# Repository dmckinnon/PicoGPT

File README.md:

# PicoGPT
I’ve wanted to learn more about the optimisation techniques that go into running modern LLMs on specialised hardware for a long time, so I recently did a technical deep dive. This involved creating and training a small (few megabytes) GPT-architecture model, which got me thinking: could I optimise such a model to run on something small? What's the smallest thing I could get a reasonable GPT to run on? 

Lo and behold, I give you a Generative Pretrained Transformer running on an ARM Cortex M33, at ~50 tokens per second generation. Let's dive in to how I achieved this.

## Contents
- [Introduction](#introduction)
- [Model structure, size, and training](#model-structure-size-and-training)
- [Porting from tflite to C++](#porting-from-tflite-to-c)
- [Can this run at all](#can-this-run-at-all)
- [Optimisations](#optimisations)
- [Circuit design and fabrication](#circuit-design-and-fabrication)
- [Conclusion](#conclusion)
- [Usage](#usage)

## Introduction
To learn deeply about LLMs I went to none other than [Karpathy](https://karpathy.ai/), his [youtube series](https://www.youtube.com/playlist?list=PLAqhIrjkxbuWI23v9cThsA9GvCAUhRvKZ) on basic LLM architecture, and of course, his [NanoGPT repository](https://github.com/karpathy/nanogpt). This is an excellent way to learn as Karpathy is clear, goes through simple steps, and the repository provides an easy playground to mess with parameters and model structure - one can see which changes affect what, like different numbers of attention heads, layers, context length, etc. The rest of this writeup assumes a considerable familiarity with the topics Karpathy goes over, Language Model architecture, Attention Heads, embedding vectors, tokens, etc. (For those who don't like youtube videos, my own writeups, mostly for my understanding, can be found [elsewhere](https://dmckinnon.github.io/LLMs-overview/) on my [site](https://dmckinnon.github.io/Tokenisation-in-LLMs/))

I'd also recently finished my [Machine Learning Business Card](https://dmckinnon.github.io/ML-Business-card/), and was struck by the thought: _could I make a NanoGPT model that ran on one of these cards?_

There's so many considerations involved in this:
- what does such a model even do? Is it too small to do anything?
- can you get a meaningful model that small? The voice recognition card has 4MB flash and ~200Kb RAM
- The base shakespeare-predictor model that NanoGPT creates, completing phrases from the works of Shakespeare based on character-tokens in a prompt, is ~40~Mb in size, with ~10 million parameters. 
- how fast will this run? My lil chip runs at 125MHz. The NanoGPT example runs on my laptop in functionally-immediate speed, but my laptop has a discrete GPU.

There's two main challenges:
1. Creating a model that can, at minimum, fit into the flash of this chip (4Mb), and probably needs to be smaller, but that also can generate coherent english sentences.
2. Getting such a model to run in real time on this tiny chip 

So, where to start? 

## Model structure, size, and training
First, can we even create a model that's really small and does something useful? I set myself a size budget of 100Kb - as in the model file (all model parameters) could not be larger than this - and twiddled with the base model. This budget comes from being ~half the RAM of the RP2040 - I'm eyeballing and thinking the code won't take much, and then we need some memory for stack, heap, etc, so 100kb seems like a good amount to aim for a priori.\ 
But what should we train it on? 100Kb model, predicting Shakespeare? That's boring, that's not much Shakespeare and also who cares. Some other pithy quotes? Amusing, but no. 

What about ... me? What if we trained the model to regurgitate facts about me? Going back to the business card idea, wouldn't it be great if my business card could just ... speak my resume to people and answer queries about that? 

I loved this idea, so I wrote up my CV, writ small (100Kb model, remember, it's not learning much), to use as the training set. 

### The base model
If we just run the prompts Karpathy has given us, to predict Shakespeare, then we get a model with:
- vocab size 65
- dataset length 1 million
- 6 layers in the model
- 6 attention heads
- 384 embedding dimensions
- ~ 10 million parameters
- ~40Mb in storage as float

### My model
The training data is the following:

```
David studied at UNSW Univeristy of New South Wales from 2012 to 2016\
What did he study?
He studied engineering and mathematics, focusing in robotics and computer vision 
David worked at Microsoft from 2016-2023
What did he work on?
At Microsoft he worked on HoloLens, using feature tracking.
At Microsoft he experimented with constellation tracking and non-inertial tracking
David work at startup Tetra in 2023
At Tetra he worked on ML graph passes, op implementations, and model zoo
David worked at Qualcomm in 2024
At Qualcomm he worked on ML graph passes and op implementations
```

dataset stats:
- length of dataset in characters: 582
- all the unique characters:  ,-.012346?ADHLMNQSTUWabcdefghiklmnoprstuvwxyz
- vocab size: 47 unique tokens, where each token is a single character

Couple notes:
- Why the questions? So that this could be legitimately queried, like a prompt could be those precise questions
- "doesn't this contain a lot of redundancy?". Yes. Yes it does. The tokenizer I'm using tokenises by characters. I want there to be examples where the characters "experimented" follow "he", but also the characters "studied" follow "he", and so on and so forth. 
- This is succinct because the model is 100kb at most, like I really have to squish it down
- Could we have more? Not sure, let's start here. I wasn't sure at the time how good a 100Kb model would be. Worst case is we overfit to this, and if this happens, I'll train on a bigger dataset

I played around with parameters. How many heads? How many embedding dimensions? How many layers? There are so many experiments to run, and I definitely did not exhaustively find the best set of parameters. But that's not my goal - I just want _something that works_. I found that the following worked:

- 1 attention head per layer
- 2 layers
- 32 embedding width
- context length 31, using a sliding window context
- 27,232 parameters
- 107Kb in storage as float

By "worked" here I mean:
- it produced reasonable predictions when prompted ... although to be honest, it's so overfit it's just regurgitating the training data. TODO examples
- it "fits" within the memory budget I have: 100Kb (ok it's 107Kb but this is close enough, I'm going to work with it)

This is a good start! Maybe I want to return to this step for a better model, but this easily fits within the flash we have - 4Mb, the matrices for individual steps fit within the RAM budget, and the results look good. So before I stress too much over getting the perfect model, let's attempt implementation. 

## Porting from tflite to C++
When running the model in NanoGPT's sample.py, there are two parts. One is the actual forward pass of the transformer, which produces a vector of logits, and the other is a loop that runs softmax over these logits, finds the probability of each vocab entry (token), samples from a distribution to get the next token, and then runs the next forward pass over the new token set. 

The first part, the actual forward pass of the transformer, is the model inference and it's here we use the model weights. The rest is just math. So to extract the model - the set of all weights, and structure of tensors and operations - in sample.py I use the following python code, where `model` is the `torch.nn` object whose `forward` function is the transformer pass inside the `mode.py` `generate` function:

```
traced = torch.jit.trace(model, x)
torch.jit.save(traced, "traced_model.pt")
```

This produces a pytorch file. Are we going to manually copy the weights from this? Well, no.\
Pytorch files are not particularly well optimised, having many redundant layers like transposes that are later cancelled by other transposes, or cast ops to int, or whatever:

I'd like to clean this model up, and made it easier to understand, for starters. Qualcomm has this marvellous platform called [Qualcomm AI Hub](https://workbench.aihub.qualcomm.com/) that can [optimise a model for a device](https://workbench.aihub.qualcomm.com/docs/hub/compile_examples.html).\
(Disclosure: no, I'm not sponsored by Qualcomm. I used to work on this product, however, and just genuinely think it's really useful)\
While the device I'm optimising for isn't available - they only have a selection of Qualcomm chips, funnily enough - this doesn't matter. All I'm really hoping to do is to strip the unnecessary layers from the model. We run it through their platform 

and now we have a tflite file! This is considerably cleaner, so the Qualcomm optimisation pass was worth it, even just for readability. From this we can identify the different parts of the transformer in each layer and consider the code for each part. 

### Layernorm
- the [layernorm](https://docs.pytorch.org/docs/2.15/generated/torch.nn.LayerNorm.html) op. Straightforward elementwise mathematical operation. (TFLite does not natively have a Layernorm op, and so breaks this out into constituent operations). This is\
$y=\frac{x-\bold{E}[x]}{\sqrt(Var[x]+\epsilon)}\times\gamma +\beta$\
The point of this operation is to normalise the data after each other operation, so there's a few of these.

```
for (size_t seq = 0; seq < seq_len; seq++) {
    const float* input_row = input + seq * embed_dim;
    float* output_row = output + seq * embed_dim;
    
    // Compute mean
    float mean = 0.0f;
    for (size_t i = 0; i < embed_dim; i++) {
        mean += input_row[i];
    }
    mean /= embed_dim;
    
    // Compute variance
    float variance = 0.0f;
    for (size_t i = 0; i < embed_dim; i++) {
        float diff = input_row[i] - mean;
        variance += diff * diff;
    }
    variance /= embed_dim;
    
    // Normalise
    float inv_std = 1.0f / sqrtf(variance + epsilon);
    for (size_t i = 0; i < embed_dim; i++) {
        output_row[i] = gamma[i] * (input_row[i] - mean) * inv_std + beta[i];
    }
}
```

### Q/K/V
- Q/K/V matrix multiplications with the embedding vectors. Matrix $\times$ vector, simple. By keeping the vectors consecutive in memory, we create a matrix, and can just use our matrix multiplication function to do this:

```
static inline void matmul(
    const float* A, size_t rows_a, size_t cols_a,
    const float* B, size_t cols_b,
    float* C
) {
    for (size_t i = 0; i < rows_a; i++) {
        for (size_t j = 0; j < cols_b; j++) {
            float sum = 0.0f;
            for (size_t k = 0; k < cols_a; k++) {
                sum += A[i * cols_a + k] * B[k * cols_b + j];
            }
            C[i * cols_b + j] = sum;
        }
    }
}

// Then to actually do the QKV projection:

const float* q_weights = qkv_weights;                           // [0:embed_dim, :]
const float* k_weights = qkv_weights + embed_dim * embed_dim;   // [embed_dim:2*embed_dim, :]
const float* v_weights = qkv_weights + 2 * embed_dim * embed_dim; // [2*embed_dim:3*embed_dim, :]

// Project to Query
matmul(input, seq_len, embed_dim, q_weights, embed_dim, query);

// Project to Key
matmul(input, seq_len, embed_dim, k_weights, embed_dim, key);

// Project to Value
matmul(input, seq_len, embed_dim, v_weights, embed_dim, value);
```

### Scaled Self-Attention
- Scaled self-attention\
[image]
This is the key attention equation:\
$Attention(Q, K, V) = softmax(\frac{QK^T}{\sqrt{d_k}})V$\
We could break this down further into a matrix multiplication, a scaling, and another matrix multiplication, but I think it's better to keep it all as one function because then we can smoosh a bunch of things together. 

```
static inline void softmax(float* input, float* output, size_t length) {
    // Find maximum value for numerical stability
    float max_val = input[0];
    for (size_t i = 1; i < length; i++) {
        if (input[i] > max_val) {
            max_val = input[i];
        }
    }
    
    // Compute exponentials and sum
    float sum = 0.0f;
    for (size_t i = 0; i < length; i++) {
        output[i] = expf(input[i] - max_val);
        sum += output[i];
    }
    
    // Normalize
    for (size_t i = 0; i < length; i++) {
        output[i] /= sum;
    }
}

// then to perform attention

const float scale = INV_SQRT_HEAD_DIM; // 1/sqrt(embed_dim)
    
// Compute Q * K^T / root(embed_dim)
// query: [seq_len, embed_dim], key^T: [embed_dim, seq_len] -> scores: [seq_len, seq_len]
for (size_t i = 0; i < seq_len; i++) {
    for (size_t j = 0; j < seq_len; j++) {
        float sum = 0.0f;
        for (size_t k = 0; k < embed_dim; k++) {
            sum += query[i * embed_dim + k] * key[j * embed_dim + k];
        }
        attention_scores[i * seq_len + j] = sum * scale;
    }
}

// Apply causal mask and softmax for each query position
for (size_t i = 0; i < seq_len; i++) {
    float* score_row = attention_scores + i * seq_len;
    
    // Apply causal mask (can only attend to previous and current positions)
    for (size_t j = i + 1; j < seq_len; j++) {
        score_row[j] = -INFINITY;
    }
    
    // Apply softmax to this row
    softmax_inplace(score_row, seq_len);
}

// Apply attention weights to values: output = attention_scores * value
// attention_scores: [seq_len, seq_len], value: [seq_len, embed_dim] -> output: [seq_len, embed_dim]
for (size_t i = 0; i < seq_len; i++) {
    for (size_t j = 0; j < embed_dim; j++) {
        float sum = 0.0f;
        for (size_t k = 0; k < seq_len; k++) {
            sum += attention_scores[i * seq_len + k] * value[k * embed_dim + j];
        }
        output[i * embed_dim + j] = sum;
    }
}

```

### Feed-Forward Network
- Feed Forward Network [image]. This is just a matrix multiplication (`Fully Connected`), a [GELU](https://docs.pytorch.org/docs/2.15/generated/torch.nn.GELU.html) elementwise operation, and then another matrix multiplication. A lot of matrix multiplication happening all over the place, so an obvious point to start improvements.

```
matmul(input, seq_len, embed_dim, up_weights, ffn_dim, hidden);
    
// Apply GELU activation in-place
apply_gelu(hidden, seq_len * ffn_dim);

// Second linear layer: output = hidden * down_weights  
// hidden: [seq_len, ffn_dim], down_weights: [ffn_dim, embed_dim] -> output: [seq_len, embed_dim]
matmul(hidden, seq_len, ffn_dim, down_weights, embed_dim, output);
```

### Residual Skip Connection
This is the `Add` operation joining those two branches together. We take the input to the whole layer, before any attention or feed-forward, and add it with the output of the whole layer.

```
static inline void add_tensors(
    const float* A,
    const float* B,
    float* C,
    size_t length
) {
    // Yeah this one's pretty simple
    // The vectors are so short it's practically not worth optimising
    for (size_t i = 0; i < length; i++) {
        C[i] = A[i] + B[i];
    }
}

// This comes in after FFN, for example
float* ffn_output = ffn_op(arena, normalized_input, up_weights, down_weights, 
                              seq_len, embed_dim, ffn_dim);
size_t total_elements = seq_len * embed_dim;
add_tensors(input, ffn_output, output, total_elements);
    
```

### Gather
This is simply indexing into an array. "Here's some indices for vocab elements, get the vocab elements they refer to".

### Putting it all together
Now all we need to do is connect those parts ... 

```
// inside Attention with residual:
qkv_projection(input, qkv_weights, query, key, value, seq_len, embed_dim);
    
// Step 2: Scaled Dot-Product Attention
scaled_dot_product_attention(query, key, value, attention_output, 
                            attention_scores, seq_len, embed_dim);

// Step 3: Output Projection
attention_output_projection(attention_output, output_weights, final_output, 
                               seq_len, embed_dim);

// Step 4: residual
size_t total_elements = seq_len * embed_dim;
add_tensors(input, attention_output, output, total_elements);

// inside FFN with residual:
layer_norm(input, normalized_input, ln_gamma, ln_beta, seq_len, embed_dim, LAYER_NORM_EPS);
float* ffn_output = ffn_op(arena, normalized_input, up_weights, down_weights, 
                              seq_len, embed_dim, ffn_dim);
size_t total_elements = seq_len * embed_dim;
    add_tensors(input, ffn_output, output, total_elements);

// Running one full layer:
// (repeat for n layers, and update parameters accordingly)
float* attn_output = attention_with_residual(
    arena, input, attn_qkv, attn_out, ln_gamma_1, ln_beta_1,
    seq_len, config->embed_dim
);

// FFN with residual connection
float* layer_output = ffn_with_residual(
    arena, attn_output, ffn_up, ffn_down, ln_gamma_2, ln_beta_2,
    seq_len, config->embed_dim, config->ffn_dim
);

```

and thats the whole model! 

## Can this run at all

Is it actually that simple? Well, let's see if this runs at all. For my first ML-on-business-card I used the [RP2040](https://pip-assets.raspberrypi.com/categories/814-rp2040/documents/RP-008371-DS-1-rp2040-datasheet.pdf), but it does software emulation of floating point hardware - that is, floating point math is actually done with 32-bit integers emulating what a dedicated floating point logic gate circuit would do. Software-floating-point will work, but be slow. Coincidentally, the next generation, the [RP2350]() chip had just come out, and this one came with a FPU coprocessor - floating point hardware! So floating point arithmetic could be performed in a single clock cycle. A dev board was acquired, a compiler was run (and run and run and run and eventually the code compiled), a chip was flashed, aaaaaand ...

|Input context length |	Time per next token |	Tokens/second
|----------------|---------------:|-----------:|
|5 tokens |	25.473 ms |	39.26
|7 tokens |	30.128 ms |	33.19
|10 tokens |	37.315 ms |	26.80
|31 tokens |	92.209 ms |	10.85

10 tokens per second!! For a basic implementation, that's a lot more than I was expecting. I'm ignoring the low context lengths, because those are not particularly useful. We want full sentences, and when a single token is a single character ... 5 characters doesn't get you much. 31 characters does. 

So, what do we do from here? Is this it? It runs, produces sentences, yay done move on?\
Absolutely not! Now we need to see just how fast we can get this model running. The main metric I'll use is tokens per second on prompt processing and decode processing, but as decode is a fixed 31-length sliding window, it doesn't make much of a difference. 

There are a number of optimisations I have in mind: multithreading, unrolling, removing intermediates, RAM residency, quantisation. The next section will go through everything I tried, including failures. 

## Optimisations

There are several benchmarks I'm using here. For some things like matrix multiplication, we can easily create a standalone benchmark. I'm also giving the model a small prompt and generating 100 output tokens based on this prompt, and we'll see how that is affected each time. 

All optimisations were also checked for accuracy, both on numerical benchmarks (computing matrices etc) and also checking token-generation output. While the output logits (the values directly from the final layer) changed slightly, the difference was never enough to change the final probabilities for each token, for the next prediction. Only optimisations that maintain this accuracy are considered. 

There are a couple of optimisations some notice are missing here; namely, quantisation and KV caches. I did consider these and ultimately rejected, and I'll address that briefly:
- Quantisation.\
Quantisation involves squashing my nice and accurate floating points into discrete little int8s. The advantages of this are namely storage - I could have four times as many parameters for the same flash size - and processing speed, as I could use the M33's DSP to do SIMD operations on int8 data, computing 4 results within one clock cycle. However, there's an accuracy cost to quantisation, and given the speeds I ended up getting with floating point, I did not consider the accuracy hit worthwhile at this stage. Perhaps for V2, where I want to attempt a bigger model.
- KV Cache\
One common optimisation in the LLM-implementation field is that of a KV cache. When generating tokens after the prompt, since we have already run over the attention of previous tokens to other previous tokens, this does not need to be recomputed, so we, well, cache the result of this and simply compute the K/V results for any new tokens. I decided against this one. Firstly, when generating tokens, I use a sliding window context of 31 tokens - therefore, any results older than 31 tokens become irrelevant, and we need to recompute the 31-token attention anyway, or do complex cache management. Recomputing is easier. Secondly, 31-token context is simply not large enough to warrant the complexity of a KV cache.

### Cache-coherent matmul
Both attention and Feed-Forward Networks rely on matrix multiplication. My thought was that to optimise for cache-coherency, as matrices tend to be stored linearly, we could write out one row of output at a time - keeping the whole row in cache - and therefore keep one row of matrix $A$ in $C = A\times B$ resident in cache as well, whilst iterating through the columns of B. That second iteration would have cache misses, but no more so than a regular iteration keeping one column of B, iterating through rows of A and rows of output. 

A nice idea in theory; it turns out, from the [datasheet](https://support.arm.com/documentation/100230/latest/) that the ARM Cortex M33, that the RP2350 is based on, has no CPU cache, and therefore ... this is irrelevant. Oh well. A nice idea.

### SRAM Residency
The RP2350 fetches weights from flash and places them into SRAM to do the matrix calculations. There is a 16 KiB cache for this, buuuuut ... what if we avoided that fetch? Each fetch from flash has a delay due to the cache (could have a miss) and the QSPI memory interface. It's not large, but we have 500Kb of SRAM and a 107Kb model. We can fit this entirely within RAM once upon startup - incurring a one-time cost - but then reuse weights with abandon, processing as many new tokens as we see fit without any extra fetch overhead. 

To achieve this, we just use a linker setting: `-DPICO_DEFAULT_BINARY_TYPE=copy_to_ram`\
Or in CMake, `pico_set_binary_type(PicoGPT copy_to_ram)`. \
This then copies all application code and constants, like weights, into SRAM upon boot. We could manually write a copy, but I prefer to not reinvent the wheel (or the memcpy).

Here's the timing, with and without:
|Configuration	|Time per token, 31-token context|	Tokens/s|
|----------------|---------------:|-----------:|
| baseline, flash/XIP|	79.852 ms|	12.52|
|SRAM code + weights|	63.907 ms|	15.65|

A considerable improvement! An expected one, but nonetheless rewarding to see. 

### Unrolling
This is essentially pipelining loops. Consider a standard matmul loop:

```
for (B matrix rows)
    for (A matrix cols)
        for (C matrix position)
            C[i,j] += a*b
```

In the inner-most loop, we do one multiplication, one addition, one store, and then check loop conditions, have a potential branch, and set up the loop again. There's almost as much overhead as there is loop calculation!

What if we were to do more per loop? Consider:

```
for (B matrix rows)
    for (4 A matrix cols)
        for (4 C matrix positions)
            C[i_1,j_1] += a_1*b_1
            C[i_2,j_2] += a_2*b_2
            C[i_3,j_3] += a_3*b_3
            C[i_4,j_4] += a_4*b_4
```

We've essentially batched this matmul, doing 4 at a time. Obviously this requires the size to be divisible by 4, but we know the size a priori so we can make this work. Now we do 4 multiplications and 4 additions per loop overhead! The multiplications in the Floating Point coprocessor take a couple of cycles, but there are multiple floating-point registers we can use so these multiplies can be pipelined so we hide the delay on those registers behind the next multiply:

```
Example with unrolling 2 at a time

Before:
cycle 1: R0 = R1*R2
cycle 2: R0 locked behind second cycle  of multiply, nothing happens
cycle 3: R4 += R0
cycle 4: loop stuff

After:
cycle 1: R0 = R1*R2
cycle 2: R0 locked, R5 = R6*R7
cycle 3: R4 += R0, R5 locked
cycle 4: R8 += R5
cycle 5: loop stuff
```

In this 'after', there's no cycle where we are just waiting - we're always doing something. This may seem small, but recall it's the inner loop of three nested loops so this happens a lot. And that's just one matmul, of three matmuls per layer, for two layers, per token. The time saving should add up. 

Does it? Let's take a look at the results:

|Configuration|	Time/token|	Tokens/s|	Speedup vs flash baseline|
|----------------|---------------:|-----------:|-----------:|
|Flash/XIP baseline|	79.852 ms	|12.52	|1.00×|
|SRAM code + weights|	63.907 ms|	15.65|	1.25×|
|Four-way matmul unrolling: FFN and attention projections|	40.826 ms	|24.49	|1.96×|

As expected, we get gainz. That's enormous though! 

What can be unrolled?\
Any loop, really. Matrix multiplications, elementwise operations like tensor addition or GELU, parts of the softmax function. Unroll everything! I realised later that I had forgotten some of the loops to unroll here, and so our speedup is technically even more.

### Fused Multiply-Accumulate
Can we make the inner loop of matmuls even faster? Until now, this inner loop of the matrix multiplication has been using two instructions: floating point multiply, and floating point add. \
But there's an important feature in this floating point coprocessor: [Fused Multiply-Accumulate](https://pip-assets.raspberrypi.com/categories/1214-rp2350/documents/RP-008373-DS-3-rp2350-datasheet.pdf), also known as `FMA` (Section 3.7.2.4).

This does exactly as it sounds, performing a multiply and accumulate (+=) all in one instruction. This should make our inner loop have half the number of instructions! That's twice as fast! It's a relatively simple change, just a compiler flag:

```
# Specifically, the ffp-contract=on is the FMA.
target_compile_options(PicoGPT PRIVATE
    -Wall -Wextra -O2 -fstack-usage -ffp-contract=on
)
```

And this will replace floating point multiplies followed by accumulates with the single instruction. 

Check results, and note that this is on top of unrolled loops:

|Measurement|	FMA off|	FMA on|	Change in elapsed time|
|----------------|---------------:|-----------:|-----------:|
|Scalar attention-projection matmul	|1.836 ms	|1.624 ms	|11.5% less|
|Four-way attention-projection matmul|	0.945 ms|	1.168 ms|	23.6% more|
|Four-way FFN-up matmul	|3.767 ms|	4.659 ms	|23.7% more|
|Generate 100 tokens, inference only	|3.432 s|	3.612 s|	5.2% more|

Oh.\
This is slower, overall.\
Hmm. \
Why is this slower?

I dug a bit but not enough to properly figure it out. It was faster than the single-multiple-accumulate per loop, but not faster than unrolling. My theory is that it uses more registers and slowed down the unrolled version with register swaps? No evidence to support this. I could dig into the assembly, but we got such a massive win from unrolling and there's more to try that if all else fails I'll come back, but otherwise ... meh. Chalk this one up as a loss. 

### Removing Intermediates/Fusing
The concept behind this idea is that we are constantly performing an operation, like adding two tensors, and then writing the result out to a third tensor in memory. The next operation will read this back from memory, perform something else on it, like some elementwise operation, and then write it back out again. \
There's a lot of inefficiency here. What if we fused the two? That is, what if we didn't have the intermediate tensor?\
For example, after FFN we have the residual skip-layer, where we add the tensor from the start of the layer back into the result from the layer. We could complete the matmul, write that out, and then loop through the tensor again and element-wise add. \
Or\
We could, while performing the matmul, add the residual to the layer-input tensor at the output of the matmul, and thereby avoid a whole separate iteration through the tensor?

Let's see this in code:

```
Before:
for (rows of B)
    for (cols of A)
        for (elems in dot product)
            C[i] += a*b

for (elems in tensor)
    C[i] += input[i]

After:
for (rows of B)
    for (cols of A)
        for (elems in dot product) 
            C[i] += a*b
            C[i] += input[i]
```
We still have to do all the operations, but what this saves is all the loop overhead - not just in an unrolling fashion, but ALL the loop overhead of a second loop. \
We can do this for the two residual skip-connections, and also the GELU operation in the middle of the FFN. 

Let's check these separately:

|FFN configuration|	Full-context time/token	|Tokens/s|	100-token inference|
|----------------|---------------:|-----------:|-----------:|
|Before fusion|	40.826 ms	|24.49	|3.432 s|
|Buffer reuse + fused residual and fused GELU|	41.863 ms	|23.89	|3.517 s|
|Buffer reuse + fused residual, separate GELU	|40.330 ms	|24.80	|3.388 s|

So the skip connection fusing works, albeit for a marginal gain. Why doesn't GELU? GELU uses the [C++ `erff` function](https://en.cppreference.com/cpp/numeric/math/erf), which is register heavy. This works on its own, but when we are trying to preserve four separate accumulated values ... that costs extra registers which therefore cannot be used during a register heavy function. I didn't dig into the assembly here, but my best guess is that there was some use of SRAM to hold register values while `erff` was computed, reducing time savings under fused-unrolling.

Oh well. We can still unroll the GELU on its own and get an already-proven win there - that is, finish the unrolled matmul, save an intermediate, perform GELU unrolled on its own loop (so each of four `erff` calls in the loop has full register access), and then move on to the next matmul. How does this perform?

|Configuration|	Time/token	|Tokens/s	|Speedup vs flash baseline|
|----------------|---------------:|-----------:|-----------:|
|Flash/XIP baseline	|79.852 ms|	12.52	|1.00×|
|SRAM code + weights|	63.907 ms|	15.65	|1.25×|
|Four-way matmul unrolling: FFN and attention projections|	40.826 ms	|24.49|	1.96×|
|FFN buffer reuse, fused residual, separate GELU|	40.330 ms	|24.80	|1.98×|

The fused residual is a pretty small gain, but again - doesn't hurt us, doesn't overly complicate the code, so I'm going to keep this in.

### Multithreading
Another seemingly obvious win. Until now, all algorithms have run on a single core - which we needed to clearly know what the speedup was, so this one has to come last. 

The Cortex M33 has two cores, each with a floating point coprocessor. There are no CPU caches, as mentioned previously, and both cores just read and write directly to SRAM. All we need to do is split the loops we intend to multi-thread correctly so no memory contention occurs, and this should just fall into place. We'll multithread the matrix multiplication loops - unrolled and with fused intermediates, so this means multithreading several implementations - and try the elementwise GELU loop. The softmax ... is finicky enough and doesn't take enough time for this to be worth it. I profiled the whole thing, and matmul dominates. Softmax was a mere 5% of time, to the ~60% of time spent on matmul. 

How should we split up the matrix multiplication? GELU loop is easy - first half to one core, second half to other core. Matrices, though - the cores need to share one matrix entirely. \
The way that sounds best on paper is, for $C = A\times B$, to split $A$ between the two cores, share $B$, and then also split the output $C$. The split would occur vertically through the matrix:

$$
C = AB =
\left[\begin{array}{c}
A_1 \\ \hline A_2
\end{array}\right] B
=
\left[\begin{array}{c}
A_1 B \\ \hline A_2 B
\end{array}\right]
=
\left[\begin{array}{c}
C_1 \\ \hline C_2
\end{array}\right]
$$

where $A_1, A_2 \in \mathbb{R}^{(m/2) \times k}$ and $C_1, C_2 \in \mathbb{R}^{(m/2) \times n}$. Thread $i$ computes $C_i = A_i B$.

This works because $A$ is laid out row by row in memory, so by giving the first half of the rows to one core, we give it a contiguous memory block, and the second half of the rows is also one contiguous memory block going to the second core. There's no memory contention or overlap. $C$ is laid out the same way.\
There's some nuance I'm brushing over here with setting up the second core to run, passing jobs to it, etc, but we don't need to go into that. The code is simple enough, and the point here is the theory of splitting and multithreading.

Let's take a look at the results:

|Execution	|Full-context time/token|	Tokens/s	|100-token inference|
|----------------|---------------:|-----------:|-----------:|
Single core|	37.862 ms|	26.41	|3.195 s|
Two cores	|24.018 ms	|41.64	|2.024 s|

A clear win. We didn't really expect anything else - doing half the work simultaneously with the other half of the work, with minimal overhead.

### Ignoring unused output
Almost an afterthought, this one. In the base implementation, we compute a whole vector of output logits, softmax to get the probabilities per index, and then choose a token per index. But previous indices have already been computed! We only need the last token. 

Simple: don't softmax the whole vector, just the last entry, and then only compute for this token. Removes unneeded compute. 

Let's check the speedup we get:
|Measurement|	Before	|Last-position-only output|
|----------------|---------------:|-----------:|
|Full-context time/token	|24.018 ms|	20.779 ms|
|Tokens/second	|41.64	|48.13|
|100-token inference	|2.024 s	|1.749 s|

Saves a few hundred milliseconds over the 100 token generation. Not terrible, not great - much like reading 3.6 roentgens on a dosimeter. But it causes no harm, and it is objectively faster, so we'll keep it. 

For now, I'm considering optimisation done.

## Circuit design and fabrication
I'm using the same basic concept for the board as with my previous [card](https://dmckinnon.github.io/ML-Business-card/) - the USB C port in the corner, thin enough to slot into a USB male connector. There's a couple of big differences:

<image>

1. This uses the RP2354, not RP2350. What's the difference? The 2354 has 2MB of flash built in, instead of needing an external flash chip. It's not much, and I have spare flash chips sitting around, but it makes circuit design and routing just that little bit simpler
2. I'm breaking out all the rest of the chip's GPIO. The intention here is that this board is reusable as a Raspberry Pi Pico 2 dev board, just a nice touch to whoever you give this away to, OR if I just happen to need another dev board and my main one is tied up in another project. Reusability is nice. 

I used [PCBWay](https://www.pcbway.com) for fabrication. I've talked about [using them before](), and choose them each time. It's such an easy interface and experience:

- to get a quote, just put in board dimensions and other details like colour, and approximate price is ready for you
- to get the board itself, [export and upload all necessary files from KiCad](https://www.pcbway.com/blog/PCB_Design_Tutorial/How_to_Export_Gerber_and_Production_Files_in_KiCad.html) - there might be some clarification but they'll help you through issues
- board is at your door not long after. They even have the option of doing all the components for you (i still do this myself, but it's just a preference)\

Here's the finished board! 

TODO add image
<image>

It's easy to flash, and I'm really happy with Raspberry Pi for this one - holding the BOOTSEL button puts it in flashing mode and it appears as a storage device on the computer. Drag and drop the binary, it reboots, and then runs. See below for [Usage](#usage)

## Conclusion
I'm really pleased with how this turned out. I never got to the original idea that kicked it off - using the DSP to accelerate a quantised version to reasonable speeds - but this was still fun. This project started with more than 5 seconds for generating a hundred tokens, and ended up with 1.7s.\
The model is definitely smaller than it could be, and considerably overfit, so it comes across as too regurgitative of the training data. But the optimisations drastically speed things up, and that proves a good initial point - I could use a much bigger model, and still get reasonable speed. \
Other tech workers have seen this demonstrated and were delighted or impressed at the concept and execution, also proving the point that it's a useful exercise and gets the attention of a potential hiring manager. 

### What next
As mentioned, the model is small and overfit, and runs far faster than necessary. Given that the chip I used has 2Mb flash, what I'd like to try next is a _much_ bigger model - perhaps a whole megabyte, perhaps even more. I'd practically write my biography, so far more detail and training data, and have it learn that to answer any query deeply. Then there's problems to reckon with like paging the weights in and out of flash with one core while the other core performs matmuls, and we might need to make more serious optimisations, cos there's so much more model to process. It'll run a whole lot slower, but this would be a fun test of just how big I can go and maintain something like, say, 10 tokens per second generation speed. 

### A note about AI usage
Generative AI was used in this project. There's an open philosophical discussion about how much that makes this "my" project vs ... well, who do we credit for the AI part? The data it trained on? Anyway, the point here is not to reopen that box ...\
How was it used?\
I did some code generation, but crafted the main ideas, and hand-wrote some of the code myself. Let me give some examples:

- "I'd like to try unrolling the matmul loops. Instead of just accumulating one value per loop, let's try four. Can you implement this on each matmul loop and also the loop that performs the GELU?"\
I see this as my idea and thought process, and just me skipping the mechanical effort of adding in
```
C[i_1] += a_1*b_1;
C[i_2] += a_2*b_2;
C[i_3] += a_3*b_3;
```
multiple times across several files. We all know that's error prone and not fun. The agent may have made an error, but I can review this pretty quick as its a small project.

- I wrote the original multithread code that split the matrices and ran the second half on the second core, for one matmul, and then asked the agent to do the same for the matmul-with-residual impl, and also tidy up the interface. It suggested an improved way; I went with this.

- More abstractly, I asked for a build script, and some pretty-printing of results so I could read them better. I've handwritten a lot of `printf` stuff in the past; I don't want to manually do all that again. 

We can quibble back and forth about how much this makes this "my" project, but I at least wanted to be clear about the workload split. 

## Usage

### Build and serial usage

FIX THE BELOW NONSENSE
### Makefile versus CMake

There are two build entry points in [PicoGPT/](PicoGPT/), targeting different
machines:

| Entry point | Purpose | Output |
|-------------|---------|--------|
| [Makefile](PicoGPT/Makefile) | Hand-written rules for native GCC, tests and extraction | Linux/host executables such as `gpt_model` |
| [CMakeLists.txt](PicoGPT/CMakeLists.txt) | Configure the Pico SDK, cross-compiler, board, libraries and memory layout | RP2350 firmware: ELF, UF2, map file |

Make executes build rules. CMake generates those rules for a backend such as
Make or Ninja. Thus the Pico build can also contain a generated Makefile,
but it is not the hand-written host Makefile. Use `cmake --build <directory>`
so CMake invokes the correct backend; plain `make` in this source directory
builds the host program, not the Pico firmware.

The [shell wrapper](PicoGPT/build_and_run.sh) now deliberately builds and runs
the native host demo. Firmware must be copied to the Pico rather than executed
as a Linux program.

Native commands (run in WSL for this checkout):

```sh
cd "$HOME/PicoGPT/PicoGPT"
make -B gpt_model
./gpt_model
# Equivalent host build/run:
bash build_and_run.sh

# Numerical tests, with the current dual-core dispatch exercised on host threads:
make parity-test PYTHON=./gpt_venv/bin/python \
  CFLAGS='-Wall -Wextra -Werror -O2 -std=c99 -ffp-contract=off -DGPT_MATMUL_UNROLL4=1 -DGPT_ATTENTION_UNROLL4=1 -DGPT_FFN_FUSE_GELU=0 -DGPT_MULTICORE=1'
```

The host demo is still a diagnostic program. The interactive USB console below
is implemented in [pico_main.c](PicoGPT/pico_main.c).

### Interactive Pico 2 firmware

Configure the SRAM-resident, dual-core, separate-GELU, unrolled implementation:

```sh
cd "$HOME/PicoGPT/PicoGPT"
cmake -S . -B build/pico-serial-2.3.1 \
  -DPICO_SDK_PATH="$HOME/.pico-sdk/sdk/2.3.1" \
  -DPICO_TOOLCHAIN_PATH="$HOME/.pico-sdk/toolchain/15_2_Rel1" \
  -DPICO_BOARD=pico2 -DCMAKE_BUILD_TYPE=Release \
  -DPICO_DEFAULT_BINARY_TYPE=copy_to_ram \
  -DPICOTOOL_FORCE_FETCH_FROM_GIT=ON \
  -DGPT_MATMUL_UNROLL4=ON -DGPT_ATTENTION_UNROLL4=ON \
  -DGPT_FFN_FUSE_GELU=OFF -DGPT_MULTICORE=ON -DGPT_PROFILE_ENABLED=OFF
cmake --build build/pico-serial-2.3.1 --parallel 4
```

SDK/compiler paths are specific to the local installation; adjust them on
another machine. The toolchain host architecture here is aarch64. The
`PICOTOOL_FORCE_FETCH_FROM_GIT` option builds the SDK's build-only picotool,
avoiding the extension-provided executable's missing `libusb` dependency in
this WSL environment. The first configuration needs network access.

After configuration, only the `cmake --build ...` command is needed to rebuild.
Use a new build directory when changing SDK/compiler versions to avoid mixing
cached paths.

The flashable image is `PicoGPT/build/pico-serial-2.3.1/PicoGPT.uf2`.
Hold BOOTSEL while connecting the Pico 2, copy the UF2 onto its RP2350 drive,
and then open the USB serial port. A 115200 baud terminal setting is conventional
(USB CDC is not clocked by that UART setting). Enable DTR, disable local echo,
and send lines terminated by CR, LF or CRLF. In WSL, Windows may own the serial
device; using a Windows terminal is fine.

On connection, the firmware shows help and `pico>`. It does **not** automatically
run benchmarks or generate text.

| Input, followed by Enter | Behavior |
|--------------------------|----------|
| `/random` | Generate 100 new characters from a single newline token with a fresh seed |
| `What did he study?` | Generate 100 new characters using that exact prompt |
| `/repeat` | Reuse the last successful prompt and seed |
| `/bench` | Run matmul benchmarks, reference check, seed-42 generation and memory reports |
| `/memory` | Print current runtime memory diagnostics |
| `/profile` | Run stage and SRAM-bus profiling, if compiled in |
| `/help` | Show commands and input limits |

The former immediate `r` and `p` shortcuts are replaced by slash commands so
ordinary prompt characters are not intercepted. Commands require Enter.
Backspace/DEL edits a line; Ctrl-C cancels the **input line**, not an inference
already running. Empty lines do nothing. Wait for `pico>` before sending the
next request; there is no concurrent command-input task during generation.

Prompts must contain **1-31 characters** from the exact, case-sensitive
[47-character vocabulary](PicoGPT/gpt_vocab.c). Unsupported characters are
rejected with their byte value and position. Non-ASCII/control input and lines
longer than 31 characters are rejected as whole lines, never silently truncated.
After such an error, press Enter or Ctrl-C to start a new line. Reconnecting
clears a partially entered line.

Every successful request produces **100 new model-sampled characters**, not
100 total characters including the prompt. The model uses the latest 31 tokens
as a rolling context. Temperature remains 0.8. `/random` and custom prompts
obtain a seed from the SDK `pico_rand` API, using RP2350 entropy sources, and
print that seed. Output is sampled from model probabilities, not from a uniform
character distribution. Different seeds may still produce the same text.
`/repeat` is reproducible with the same firmware; it survives a serial reconnect,
not a power cycle. `/bench`, errors and diagnostic commands do not overwrite
the remembered prompt/seed.

### Timing and writeup measurements

Each generation prints three separate figures:

- **Model processing:** time inside `gpt_inference` across all new tokens,
  excluding sampling, output and input entry.
- **Token sampling:** time selecting tokens from the logits, including the
  sampling softmax and RNG calls, excluding text output.
- **Total generation:** elapsed generation-loop time including model calls,
  validation, sampling, output calls, context updates and bookkeeping.
  This excludes seed acquisition, the printed header, and typing the prompt;
  it does not guarantee all buffered USB output has reached the terminal.

These are elapsed times on core 0, not sums of both cores' CPU time. Inference
includes the completion wait for parallel kernels. A failed generation
explicitly reports failure, the number of characters completed, and timings
for the attempted work. Normal runs omit benchmark and arena dumps; `/bench`
retains those measurements and the fixed seed 42 for repeatable writeup runs.

An interactive profiling image is also available at
`PicoGPT/build/pico-serial-profile-2.3.1/PicoGPT.uf2`. To rebuild it, use the
same configuration command with `-B build/pico-serial-profile-2.3.1` and
`-DGPT_PROFILE_ENABLED=ON`, then build that directory. Send `/profile` and
Enter. Profiling changes code layout and timing even when capture is inactive;
use the nonprofiling image for final performance figures.

Both images retain the 144 KiB arena (observed model peak **107,216 bytes**)
and guarded 4 KiB stacks for each core. The first interactive build reserves
**311,484 bytes of main RAM** and uses **159,264 bytes of flash**. The profiling
variant reserves **315,772 bytes of main RAM** and uses **163,344 bytes of flash**.
Stack reservations are in separate scratch banks and are additional to the
main-RAM figures. These sizes are build-specific.

All 22 host tests pass in multicore mode, including numerical comparisons for
prompted generation, line limits/editing/reconnection, random-seed replay,
on-demand diagnostics, and timing accounting. AddressSanitizer and
UndefinedBehaviorSanitizer also pass. Host serial/RNG/clock shims validate logic,
not USB hardware behavior, entropy quality, or on-board timing; those still
require testing this image on the Pico.

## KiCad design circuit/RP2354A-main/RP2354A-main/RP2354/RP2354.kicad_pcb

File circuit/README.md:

# QR artwork for KiCad

From the repository root, using Python 3.9 or newer:

```sh
python -m pip install -r circuit/requirements.txt
python circuit/qr_code.py "https://example.com" --size-mm 20 -o circuit/qr.svg
```

Replace the URL with your own text or link. `--size-mm` sets the total square
size, **including** the four-module quiet zone. Error correction defaults to M;
use `--error-correction L`, `M`, `Q`, or `H` to change it. Longer payloads and
higher error correction can require more modules at the same physical size.
The command reports the resulting module width; check it against your board
manufacturer's minimum silkscreen feature size.

The two steps can also be used from Python (with `circuit` on the import path):

```python
from pathlib import Path
from qr_code import generate_qr, matrix_to_svg

matrix = generate_qr("https://example.com")
Path("qr.svg").write_text(matrix_to_svg(matrix, size_mm=20), encoding="utf-8")
```

This converts the generated QR matrix, not an existing PNG or JPEG. There is no
image tracing or Pillow dependency. SVGs contain only filled, unstroked
rectangles, with adjacent dark modules merged horizontally.

## Import into KiCad

1. In the PCB Editor, select **File > Import > Graphics** and choose the SVG.
2. Select your intended layer (usually **F.Silkscreen**) and keep the import
   scale at **1.0**. Check the physical size after placement.
3. Keep the entire blank margin clear of text, pads, tracks, and other artwork.
   The SVG has **no white background**: blank modules and the quiet zone do not
   create any objects or enforce a KiCad keepout.
4. Inspect the Gerber output and test scanning a sample at actual size, ideally
   on the finished board. Avoid tiny modules; shorten the URL or enlarge the
   QR code if needed.

SVG black means "draw on the selected layer", not black ink. White silkscreen
on a dark board reverses the intended QR contrast and may not scan reliably
with all readers. Prefer a dark-on-light process where possible and test the
actual finish. Copper and solder-mask layers have different fabrication
effects; importing this file does not create pads or mask openings for you.

See the [KiCad PCB Editor manual](https://docs.kicad.org/9.0/en/pcbnew/pcbnew.html)
for graphics import options.

## Tests

```sh
python -m unittest discover -s circuit -p 'test_qr_code.py'
```

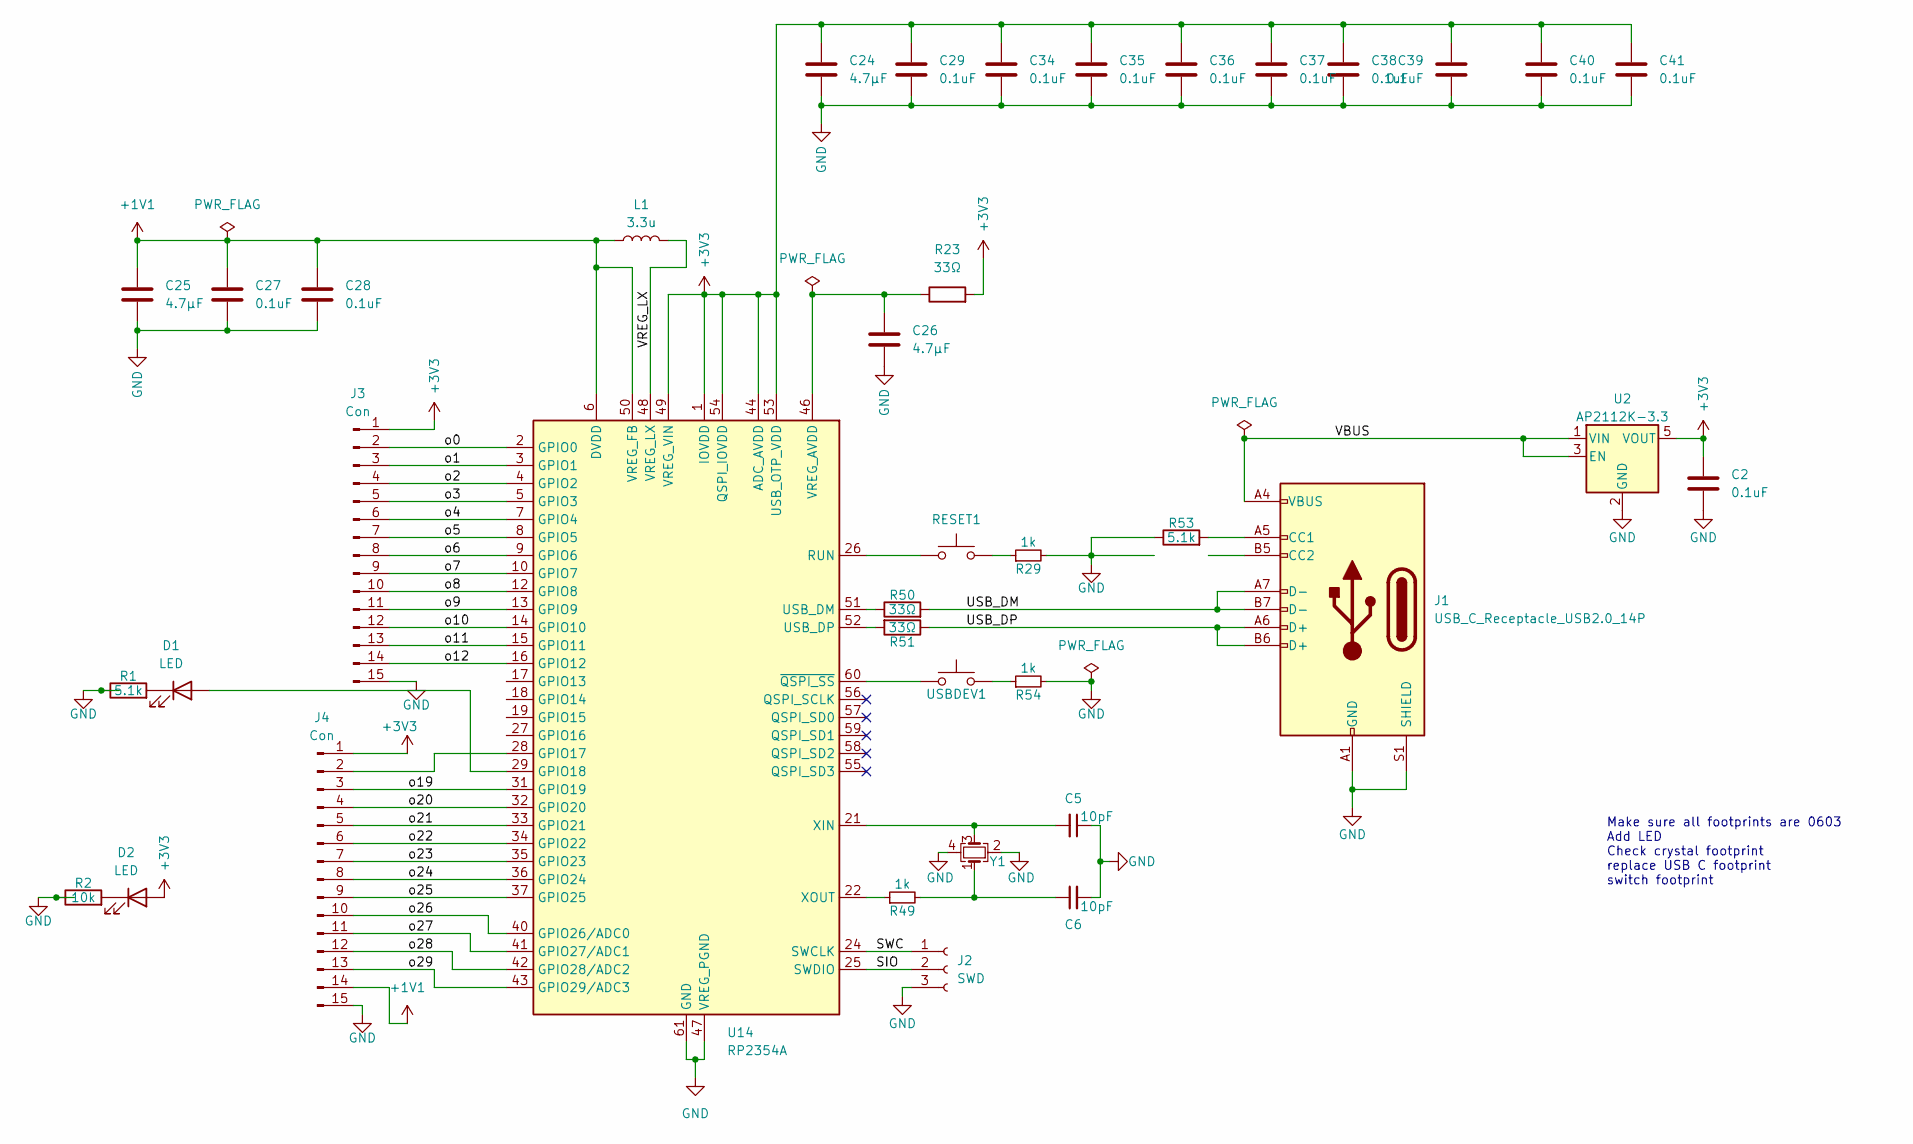
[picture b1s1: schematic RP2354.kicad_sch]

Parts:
C2, C27, C28, C29, C34, C35, C36, C37, C38, C39, C40, C41: 0.1uF; C_0603_1608Metric; MPN CL05B104KA5NNNC
C5, C6: 10pF; C_0603_1608Metric; MPN CL10C100JB8NFNC
C24, C25, C26: 4.7μF; C_0603_1608Metric; MPN GRM155D80E475ME47J
D1, D2: LED; LED_0603_1608Metric
J1: USB_C_Receptacle_USB2.0_14P; usb_c_board; MPN TYPE-C-31-M-14
J2: SWD; PinHeader_1x03_P2.54mm_Vertical
J3, J4: Con; PinHeader_1x15_P2.54mm_Vertical
L1: 3.3u; R_0805_2012Metric; MPN AOTA-B201610S3R3-101-T
R1, R53: 5.1k; R_0603_1608Metric; MPN RC0402FR-075K1L
R2: 10k; R_0603_1608Metric; MPN RC0402FR-075K1L
R23, R50, R51: 33Ω; R_0603_1608Metric; MPN RC0402FR-0733RL
R29, R49, R54: 1k; R_0603_1608Metric; MPN RT0603FRE101KL
RESET1: SW_Push; SW_1P1S_SMD; MPN KMR241G LFS
U2: AP2112K-3.3; SOT-23-5; MPN AP2112K-3.3TRG1
U14: RP2354A; QFN-60-1EP_7x7mm_P0.4mm_EP3.4x3.4mm; MPN SC1511(13)-A4
USBDEV1: SW_Push; SW_1P1S_SMD; MPN KMR241G LFS
Y1: Crystal; Crystal_SMD_Abracon_ABM3C-4Pin_5.0x3.2mm; MPN ABM8-272-T3

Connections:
+1V1: C25.1, C27.2, C28.2, J4.14, L1.1, U14.6 (DVDD), U14.23 (DVDD), U14.39 (DVDD), U14.50 (VREG_FB)
+3V3: C2.2, C24.1, C29.2, C34.2, C35.2, C36.2, C37.2, C38.2, C39.2, C40.2, C41.2, D2.2 (A), J3.1, J4.1, R23.2, U2.5 (VOUT), U14.1 (IOVDD), U14.11 (IOVDD), U14.20 (IOVDD), U14.30 (IOVDD), U14.38 (IOVDD), U14.44 (ADC_AVDD), U14.45 (IOVDD), U14.49 (VREG_VIN), U14.53 (USB_OTP_VDD), U14.54 (QSPI_IOVDD)
/SIO: J2.2, U14.25 (SWDIO)
/SWC: J2.1, U14.24 (SWCLK)
/USB_DM: J1.A7 (D-), J1.B7 (D-), R50.2
/USB_DP: J1.A6 (D+), J1.B6 (D+), R51.1
/VBUS: J1.A4 (VBUS), J1.A9 (VBUS), J1.B4 (VBUS), J1.B9 (VBUS), U2.1 (VIN), U2.3 (EN)
/VREG_LX: L1.2, U14.48 (VREG_LX)
/o0: J3.2, U14.2 (GPIO0)
/o1: J3.3, U14.3 (GPIO1)
/o2: J3.4, U14.4 (GPIO2)
/o3: J3.5, U14.5 (GPIO3)
/o4: J3.6, U14.7 (GPIO4)
/o5: J3.7, U14.8 (GPIO5)
/o6: J3.8, U14.9 (GPIO6)
/o7: J3.9, U14.10 (GPIO7)
/o8: J3.10, U14.12 (GPIO8)
/o9: J3.11, U14.13 (GPIO9)
/o10: J3.12, U14.14 (GPIO10)
/o11: J3.13, U14.15 (GPIO11)
/o12: J3.14, U14.16 (GPIO12)
/o19: J4.3, U14.31 (GPIO19)
/o20: J4.4, U14.32 (GPIO20)
/o21: J4.5, U14.33 (GPIO21)
/o22: J4.6, U14.34 (GPIO22)
/o23: J4.7, U14.35 (GPIO23)
/o24: J4.8, U14.36 (GPIO24)
/o25: J4.9, U14.37 (GPIO25)
/o26: J4.10, U14.40 (GPIO26/ADC0)
/o27: J4.11, U14.41 (GPIO27/ADC1)
/o28: J4.12, U14.42 (GPIO28/ADC2)
/o29: J4.13, U14.43 (GPIO29/ADC3)
GND: C2.1, C5.1, C6.2, C24.2, C25.2, C26.2, C27.1, C28.1, C29.1, C34.1, C35.1, C36.1, C37.1, C38.1, C39.1, C40.1, C41.1, J1.A1 (GND), J1.A12 (GND), J1.B1 (GND), J1.B12 (GND), J1.S1 (SHIELD), J2.3, J3.15, J4.15, R1.1, R2.1, R29.2, R53.1, R54.2, U2.2 (GND), U14.47 (VREG_PGND), U14.61 (GND), Y1.2, Y1.4
unnamed: C6.1, R49.2, Y1.1
unnamed: D1.2 (A), U14.29 (GPIO18)
unnamed: D1.1 (K), R1.2
unnamed: D2.1 (K), R2.2
unnamed: J1.A5 (CC1), R53.2
unnamed: J4.2, U14.28 (GPIO17)
unnamed 39: R29.1, RESET1.2; also elsewhere on the board
unnamed 40: R54.1, USBDEV1.2; also elsewhere on the board
unnamed 41: RESET1.1, U14.26 (RUN); also elsewhere on the board
unnamed: R50.1, U14.51 (USB_DM)
unnamed: R51.2, U14.52 (USB_DP)
unnamed: C26.1, R23.1, U14.46 (VREG_AVDD)
unnamed: C5.2, U14.21 (XIN), Y1.3
unnamed: R49.1, U14.22 (XOUT)
unnamed 47: U14.60 (~QSPI_SS), USBDEV1.1; also elsewhere on the board

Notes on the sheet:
Make sure all footprints are 0603 Add LED Check crystal footprint replace USB C footprint switch footprint

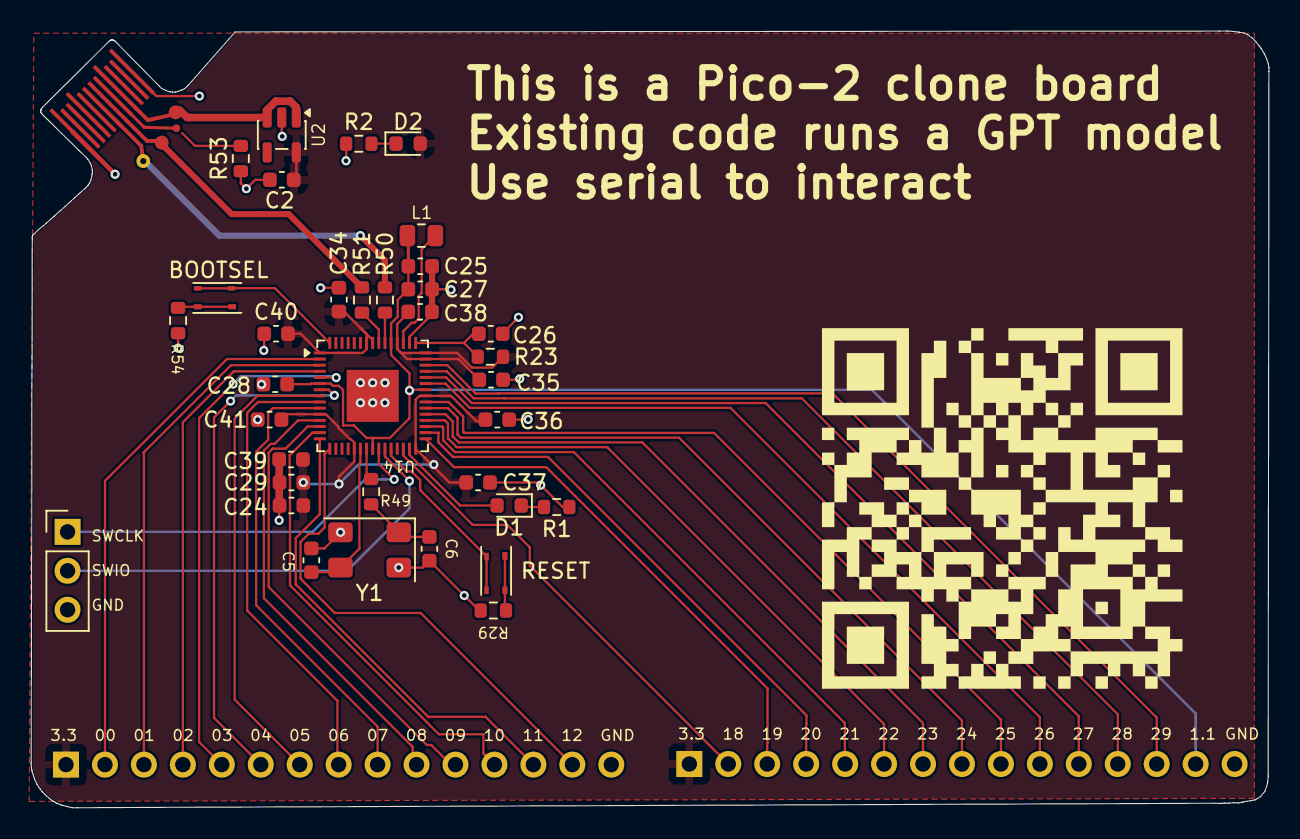
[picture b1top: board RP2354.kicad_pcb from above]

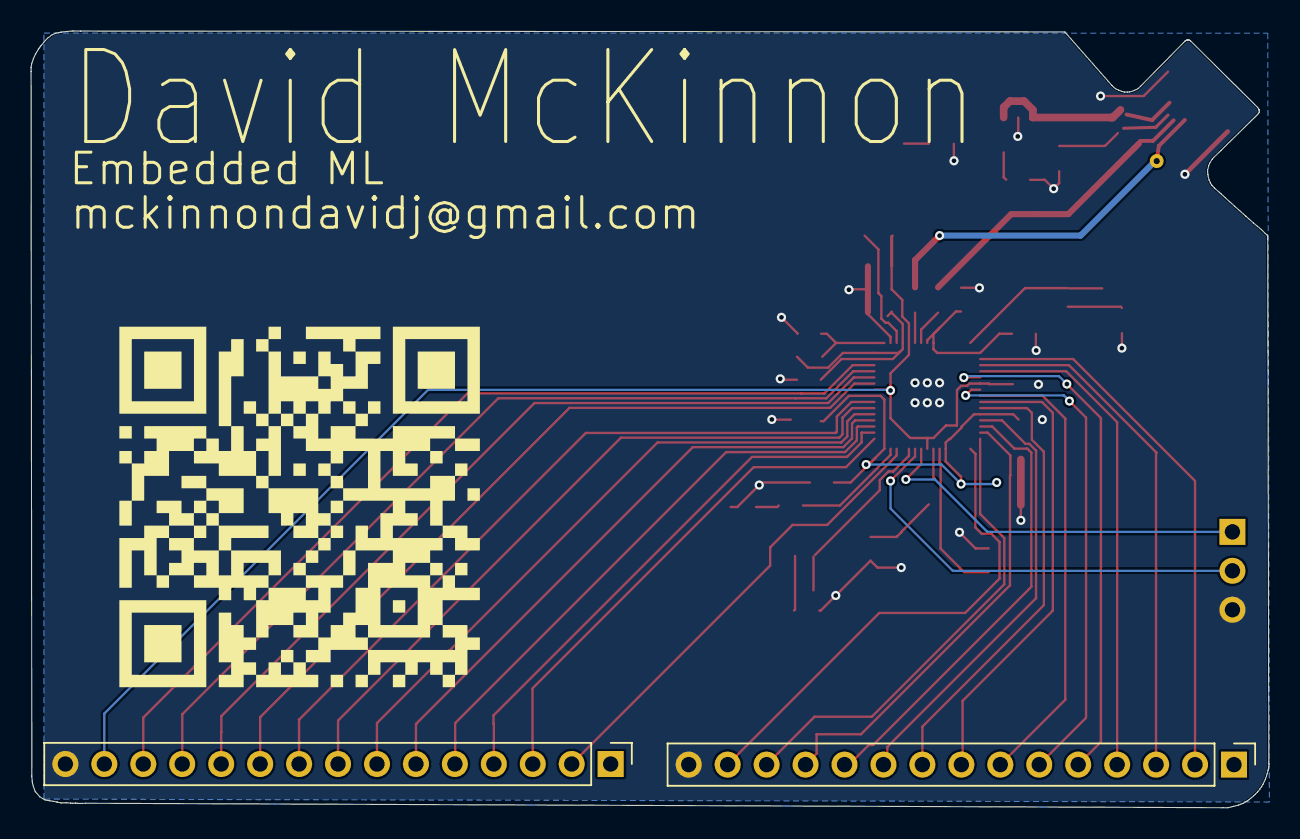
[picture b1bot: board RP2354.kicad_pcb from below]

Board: 2 copper layers, 80.7 x 50.6 mm, 38 parts (2 on the bottom side), 48 nets.

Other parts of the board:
BOOTSEL: SW_Push; SW_1P1S_SMD
RESET: SW_Push; SW_1P1S_SMD

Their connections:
unnamed 39: RESET.2; also elsewhere on the board
unnamed 40: BOOTSEL.2; also elsewhere on the board
unnamed 41: RESET.1; also elsewhere on the board
unnamed 47: BOOTSEL.1; also elsewhere on the board

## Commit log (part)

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2025-08-16 adding initial files
2025-08-16 gitignore
2025-08-16 comments
2025-11-13 test files
2025-12-19 Got things basically running. Checkpoint
2026-01-16 new files
2026-01-26 Adding quant files and changelog to annotate this
